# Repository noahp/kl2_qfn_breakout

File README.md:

kl2_qfn_breakout
================

Breakout for Freescale Kinetis MKL24Z64VFM4 in 32-QFN package.

http://www.freescale.com/webapp/sps/site/prod_summary.jsp?code=KL2  

kl24 part
=====
mouser
-----
http://www.mouser.com/ProductDetail/Freescale-Semiconductor/MKL24Z64VFM4/?qs=sGAEpiMZZMuoKKEcg8mMKCTlPPZAritFsZ2raHyVNYo%3d

digkey
-----
http://www.digikey.com/product-search/en?x=-1066&y=-70&lang=en&site=us&KeyWords=MKL24Z64VFM4

manual
-----
http://cache.freescale.com/files/32bit/doc/ref_manual/KL24P80M48SF0RM.pdf?fpsp=1&WT_TYPE=Reference%20Manuals&WT_VENDOR=FREESCALE&WT_FILE_FORMAT=pdf&WT_ASSET=Documentation

part spec
-----
http://www.mouser.com/ds/2/161/KL24P80M48SF0-218435.pdf

symbol
-----
http://www.freescale.com/files/capture/pdf/mkl24z32vfm4_qfn32.pdf

package
-----
http://www.freescale.com/webapp/search.partparamdetail.framework?PART_NUMBER=MKL25Z128VFM4&buyNow=true&fromSearch=true#Package_Information

pads
-----
http://cache.freescale.com/files/shared/doc/package_info/98ASA00473D.pdf

other parts
=====
usb micro b
-----
[ebay micro b w/ mechanical](http://www.ebay.com/itm/50Pcs-Micro-USB-Type-B-Female-Socket-4-Vertical-Legs-fixed-Solder-Connectors-/171315639526?hash=item27e33534e6)  
[mouser micro b smt only](http://www.mouser.com/ProductDetail/FCI/10118192-0001LF/?qs=sGAEpiMZZMulM8LPOQ%252byk2%252bTbV8%2f2X5vivRX5xKgOBI%3d)

10 pin header
-----
http://www.mouser.com/ProductDetail/FCI/20021121-00010T4LF/?qs=sGAEpiMZZMvffgRu4KC1R10eT3mhH9PKH6si4hSOVY4%3d

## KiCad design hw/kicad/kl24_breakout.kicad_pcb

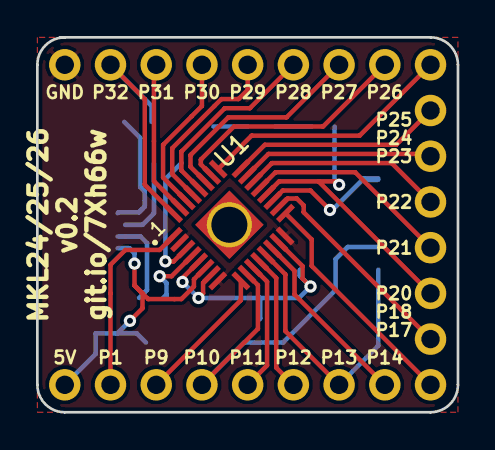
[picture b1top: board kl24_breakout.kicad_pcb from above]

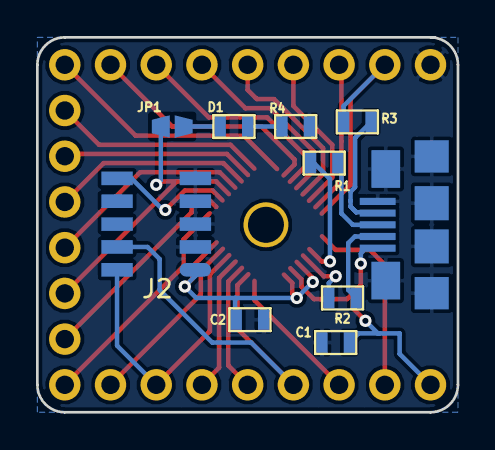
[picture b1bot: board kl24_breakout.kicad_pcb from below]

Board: 2 copper layers, 23.4 x 20.8 mm, 35 parts (10 on the bottom side), 33 nets.

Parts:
C1: 0.1uF; SM0603
C2: 2.2uF; SM0603
D1: LED; SM0603
J1: USB-micro-b; usb_micro_b_smt
J2: ARM_10PIN; ARM_10_PIN_SMT
JP1: JUMPER; jmp_small
P1, P9, P10, P11, P12, P13, P14, P17, P18, P20, P21, P22, P23, P24, P25, P26, P27, P28, P29, P30, P31, P32: TST; TEST_0.100
P33: 5V; TEST_0.100
P34: GND; TEST_0.100
R1, R2: 33R; SM0603
R3, R4: 330; SM0603
U1: MKL24Z64VFM4

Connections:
1: P1.1, U1.1
3.3V_SUPPLY: C2.1, J2.1, U1.5, U1.7, U1.15
9: P9.1, U1.9
10: J2.4, P10.1, U1.10
11: P11.1, U1.11
12: P12.1, U1.12
13: J2.2, P13.1, U1.13
14: P14.1, U1.14
17: P17.1, U1.17
18: P18.1, U1.18
20: JP1.1, P20.1, U1.20
21: P21.1, U1.21
22: P22.1, U1.22
23: P23.1, U1.23
24: P24.1, U1.24
25: P25.1, U1.25
26: P26.1, U1.26
27: P27.1, U1.27
28: P28.1, U1.28
29: P29.1, U1.29
30: P30.1, U1.30
31: P31.1, U1.31
32: P32.1, R3.2, U1.32
GND: C1.2, C2.2, J1.5, J1.6, J2.3, J2.5, J2.7, J2.9, P34.1, R4.2, U1.2, U1.8, U1.16
unnamed: R1.2, U1.3
unnamed: R2.2, U1.4
unnamed: J1.4, R3.1
unnamed: D1.1, JP1.2
unnamed: D1.2, R4.1
USB_DM: J1.2, R2.1
USB_DP: J1.3, R1.1
USB_VBUS: C1.1, J1.1, P33.1, U1.6
nreset: J2.10, U1.19

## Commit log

2013-02-28 - add usb socket part ref
2013-02-28 - add kicad proj. + mcu symbol
2013-03-01 - reference for 3.3/5v reg, add labels for some modules
2013-03-04 - add micro ab ref.
2013-03-05 - add ref for 3.3 lin reg. add usb conn.
2013-03-05 - add the rest of the ic's
2013-03-09 - add 0.9v lv battery powered supply (probably nopop)
2013-03-09 - add lipo charger circuit
2013-03-09 - add some usb things and a crystal+load caps
2013-03-10 - add global labels to all pins for breaking out to test pads.
2013-03-12 - add some labels to submodules in the schematic
2013-03-12 - populate 3.3v supply, som rearragning
2013-03-20 - fix some erc's - add test points for all micro pins
2013-03-20 - populate 5v boost converter
2013-03-22 - add spi flash
2013-03-22 - create netlist
2013-03-22 - net up all but the custom parts (and xtal)
2013-03-22 - add inductor part ref
2013-03-23 - add some sample files and the basics of a cbp project (doesn't work though) for the stm32f0.
2013-03-23 - add st f0 liib
2013-03-23 - remove layout cb file
2013-03-23 - delete unneeded files. mingw-make can't build this makefile, compilation error at assembling startup.s
2013-03-26 - try to rework usb host pwr supply, needs an extra switch i'm thinking, so i'm bailing
2013-03-26 - remove usb host pwr supply, sch done.
2013-04-12 - remove submodule lib - add vcc to arm 10 pin connector
2013-04-13 - add schottky part ref - populate some parts.
2013-04-13 - add usb pwr points
2013-04-13 - add micro ab module
2013-04-13 - add blank pcb - make footprints for all but main micro
2013-04-13 - last foot print
2013-04-14 - rebuild arm-10-pin modules and lp3985 (3.3v reg)
2013-04-14 - start pcb
2013-04-15 - switch arm 10pin header for smt version
2013-05-19 - remove lv pwr supply
2013-05-21 - add link to digikey part page
2013-05-22 - remove (local?) kicadlib
2013-05-22 - add submodule for kicadlib back
2013-05-22 - change to smt crystal
2013-05-23 - redo micro ab connector footprint
2013-05-24 - add indicator led to schematic
2013-05-24 - add indicator led + resitor and jumper to pcb
2013-06-05 - remove lipo charger
2013-06-05 - update pcb with new netlist
2013-10-05 remove spi flash (maybe sdio instead)
2013-10-10 - add net file
2013-10-11 remove 10 pin header
2013-10-12 fix up a bit
2013-10-12 fix some pcb labels
2013-10-12 more pcb
2013-10-13 all footprints placed, start wiring
2013-10-13 most connections
2013-10-13 - add schematic pdf
2013-10-14 tweak pcb
2013-10-14 remove regulator in favor of on-chip 3.3v regulator
2013-10-14 finish pcb, add label text
2013-10-14 gerber output
2013-10-14 move label text to the left a bit
2013-10-14 update schematic out
2013-10-14 add renders & files sent to fab
2013-10-15 add some decoupling caps to +5 and +3.3 and nreset update to v0.2 replot
2013-10-15 update archive
2013-10-25 - add 10k pullup on nreset
2013-10-25 - add gerbers - update pcb
2013-11-03 - remove sw
2013-11-03 - add files for building test app
2013-11-03 update project files
2013-11-04 - add flash config setting, this is 0x400-0x40f in flash memory.
2013-11-13 no submodules, fixing it
2013-11-13 remove
2013-11-13 - debug working - add pics for config
2013-11-13 - add blank readme
2013-11-14 - fix debug settings to actually work
2013-11-14 - add files from http://cubeatsystems.com/firmware/uos-lpc800/index.html
2013-11-14 - enable debugging symbols again >_<
2013-11-14 - remove os
2013-11-20 - set to 48MHz internal clock, was 24MHz by default
2013-11-20 - switch to DMX32 = 1 in MCG C4 register, this gets it pretty close to 48MHz off internal RC vs. more like 42MHz without it.
2013-11-26 picture
2013-11-28 - clean up some comments
2013-11-28 - systick
2013-11-28 - move
2013-11-28 - add interrupts, start breaking them out
2013-11-28 - systick ms timer working
2013-11-28 - add stub for main_init_spi
2013-11-29 - spi working ok
2013-11-30 - add io config for oled control pins
2013-12-04 - add ssd1306.h. - rename delay delay_ms
2013-12-09 - add sample screen from ada fruit example - correct a few mistakes, add some pin def's - major error, spi polarity should be CPOL=1 >_< , display working now
2013-12-10 -add fonts, start string print function
2013-12-11 - remove spi/oled stuff
2013-12-30 - remove power pin breakout. add arm 10 pin header.
2014-01-06 - remove crystal
2014-01-06 - edge
2014-01-06 - layout
2014-01-06 - save
2014-01-07 - change to usb-micro-b only
2014-01-07 - layout done for v0.2I think
2014-01-07 - save renders. this version is ordered.
2014-01-14 - update sch
2014-01-21 - fix some minor goofs in the pcb (extra via, extra pin 1 marker for U1)
2014-02-04 - add jlink script
2014-03-08 - try to get the uart0 setup.
2014-03-09 - usart0 working, needed to enable SIM_SOPT2 clock for usart0
